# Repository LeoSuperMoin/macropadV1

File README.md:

# macropadV1
4x5 macropad with volume slider

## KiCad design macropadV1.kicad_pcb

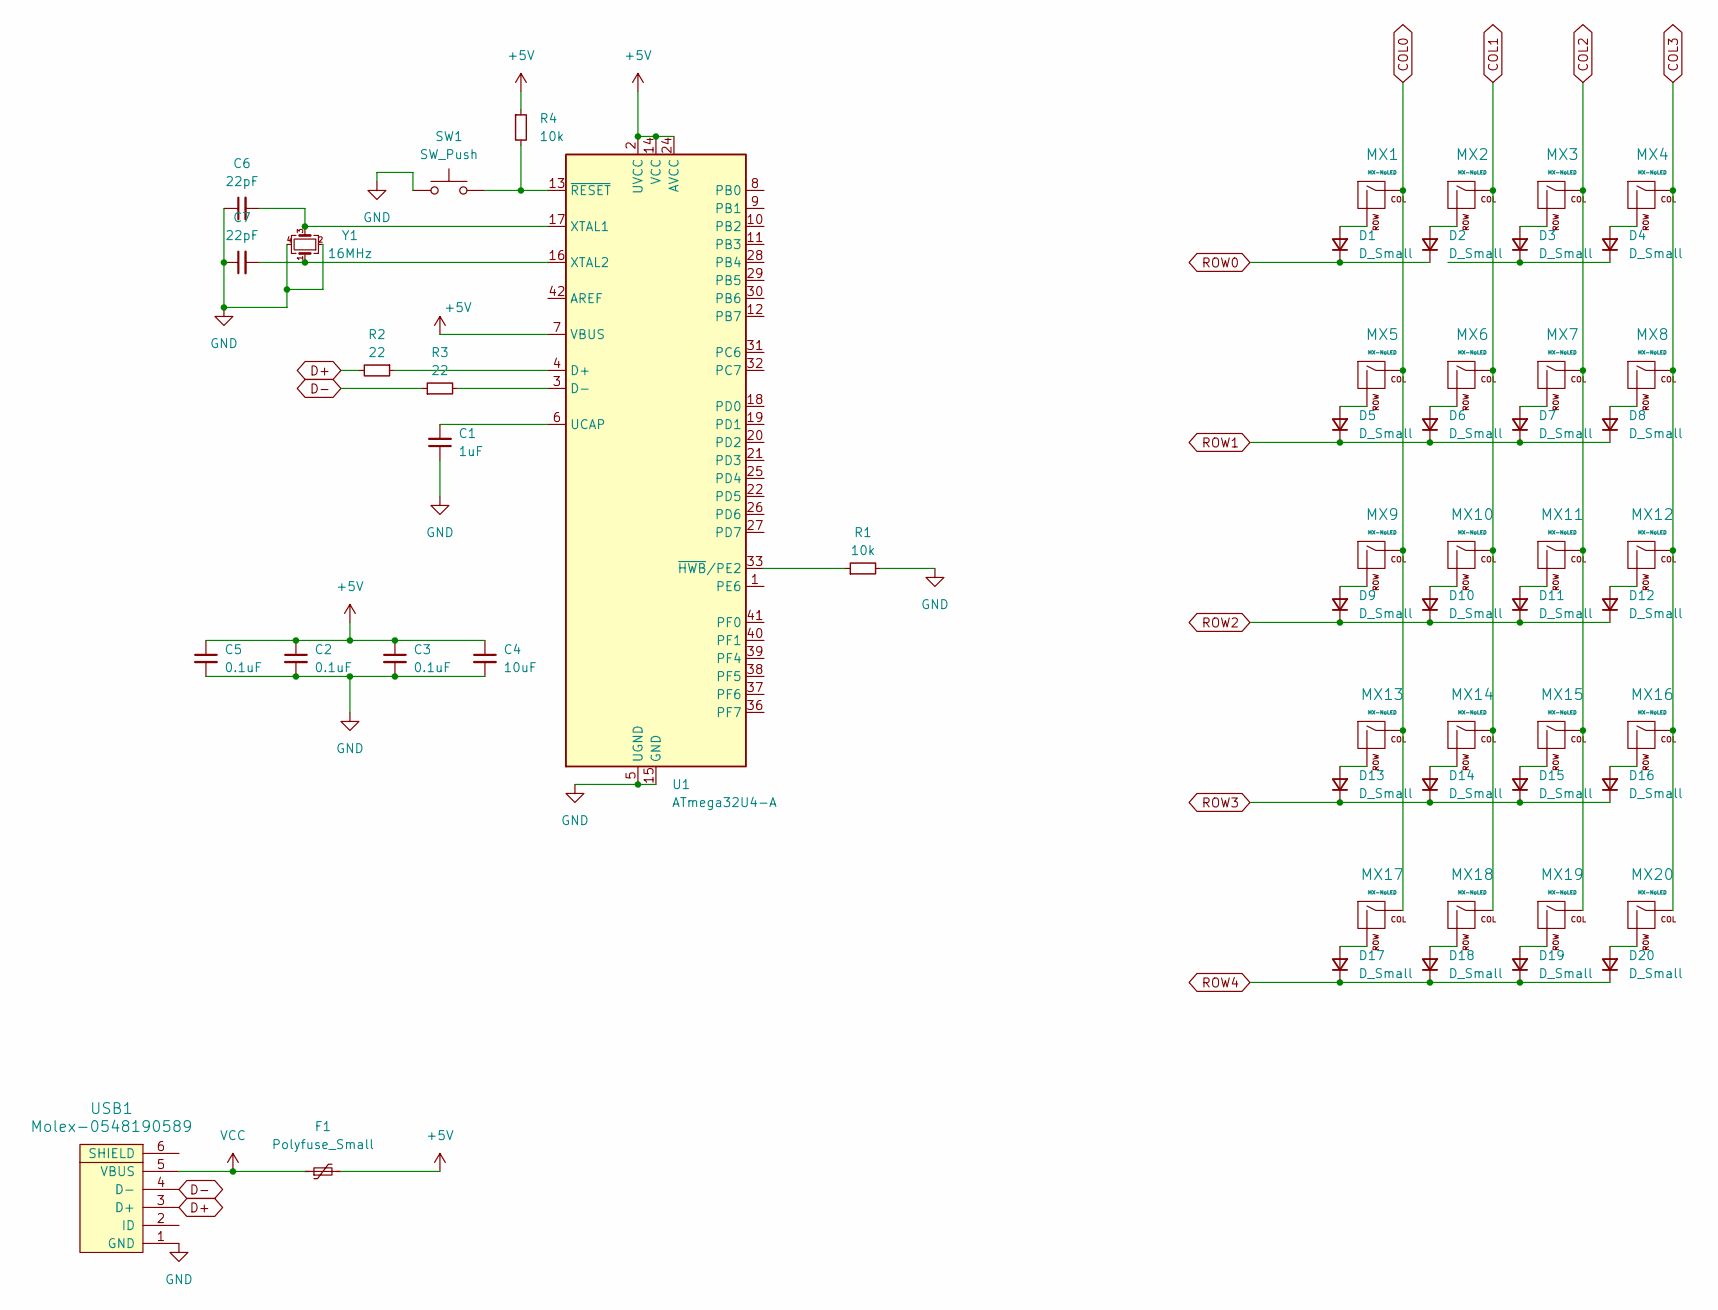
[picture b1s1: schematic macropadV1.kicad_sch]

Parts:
C1: 1uF; C_0805_2012Metric
C2, C3, C5: 0.1uF; C_0805_2012Metric
C4: 10uF; C_0805_2012Metric
C6, C7: 22pF; C_0805_2012Metric
D1, D2, D3, D4, D5, D6, D7, D8, D9, D10, D11, D12, D13, D14, D15, D16, D17, D18, D19, D20: D_Small; D_0805_2012Metric
F1: Polyfuse_Small; Fuse_1206_3216Metric
MX1, MX2, MX3, MX4, MX5, MX6, MX7, MX8, MX9, MX10, MX11, MX12, MX13, MX14, MX15, MX16, MX17, MX18, MX19, MX20: MX-NoLED; MXOnly-1U
R1, R4: 10k; R_0805_2012Metric
R2, R3: 22; R_0805_2012Metric
SW1: SW_Push; SKQG-1155865
U1: ATmega32U4-A; TQFP-44_10x10mm_P0.8mm
USB1: Molex-0548190589
Y1: 16MHz; Crystal_SMD_3225-4Pin_3.2x2.5mm

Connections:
+5V: C2.1, C3.1, C4.1, C5.1, F1.2, R4.1, U1.2 (UVCC), U1.7 (VBUS), U1.14 (VCC), U1.24 (AVCC), U1.34 (VCC), U1.44 (AVCC)
COL0: MX1.1 (COL), MX5.1 (COL), MX9.1 (COL), MX13.1 (COL), MX17.1 (COL)
COL1: MX2.1 (COL), MX6.1 (COL), MX10.1 (COL), MX14.1 (COL), MX18.1 (COL)
COL2: MX3.1 (COL), MX7.1 (COL), MX11.1 (COL), MX15.1 (COL), MX19.1 (COL)
COL3: MX4.1 (COL), MX8.1 (COL), MX12.1 (COL), MX16.1 (COL), MX20.1 (COL)
D+: R2.2, USB1.3 (D+)
D-: R3.1, USB1.4 (D-)
GND: C1.1, C2.2, C3.2, C4.2, C5.2, C6.1, C7.1, R1.2, SW1.1, U1.5 (UGND), U1.15 (GND), U1.23 (GND), U1.35 (GND), U1.43 (GND), USB1.1 (GND), Y1.2, Y1.4
unnamed: D1.2 (A), MX1.2 (ROW)
unnamed: D2.2 (A), MX2.2 (ROW)
unnamed: D3.2 (A), MX3.2 (ROW)
unnamed: D3.1 (K), D4.1 (K)
unnamed: D4.2 (A), MX4.2 (ROW)
unnamed: D5.2 (A), MX5.2 (ROW)
unnamed: D6.2 (A), MX6.2 (ROW)
unnamed: D7.2 (A), MX7.2 (ROW)
unnamed: D8.2 (A), MX8.2 (ROW)
unnamed: D9.2 (A), MX9.2 (ROW)
unnamed: D10.2 (A), MX10.2 (ROW)
unnamed: D11.2 (A), MX11.2 (ROW)
unnamed: D12.2 (A), MX12.2 (ROW)
unnamed: D13.2 (A), MX13.2 (ROW)
unnamed: D14.2 (A), MX14.2 (ROW)
unnamed: D15.2 (A), MX15.2 (ROW)
unnamed: D16.2 (A), MX16.2 (ROW)
unnamed: D17.2 (A), MX17.2 (ROW)
unnamed: D18.2 (A), MX18.2 (ROW)
unnamed: D19.2 (A), MX19.2 (ROW)
unnamed: D20.2 (A), MX20.2 (ROW)
unnamed: R2.1, U1.4 (D+)
unnamed: R3.2, U1.3 (D-)
unnamed: C1.2, U1.6 (UCAP)
unnamed: C6.2, U1.17 (XTAL1), Y1.3
unnamed: C7.2, U1.16 (XTAL2), Y1.1
unnamed: R1.1, U1.33 (~HWB/PE2)
unnamed: R4.2, SW1.2, U1.13 (~RESET)
ROW0: D1.1 (K), D2.1 (K)
ROW1: D5.1 (K), D6.1 (K), D7.1 (K), D8.1 (K)
ROW2: D9.1 (K), D10.1 (K), D11.1 (K), D12.1 (K)
ROW3: D13.1 (K), D14.1 (K), D15.1 (K), D16.1 (K)
ROW4: D17.1 (K), D18.1 (K), D19.1 (K), D20.1 (K)
VCC: F1.1, USB1.5 (VBUS)

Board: 2 copper layers, 56 parts (20 on the bottom side), 42 nets, no tracks yet.

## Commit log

2024-02-05 First Steps
    creation of the basic kicad files
2024-02-05 Add submodules
2024-02-05 Setup complete
    added neccessery libraries
2024-02-05 Electrical scheme complete
2024-02-06 Schematic done
2024-02-06 Save
    just a save in between
